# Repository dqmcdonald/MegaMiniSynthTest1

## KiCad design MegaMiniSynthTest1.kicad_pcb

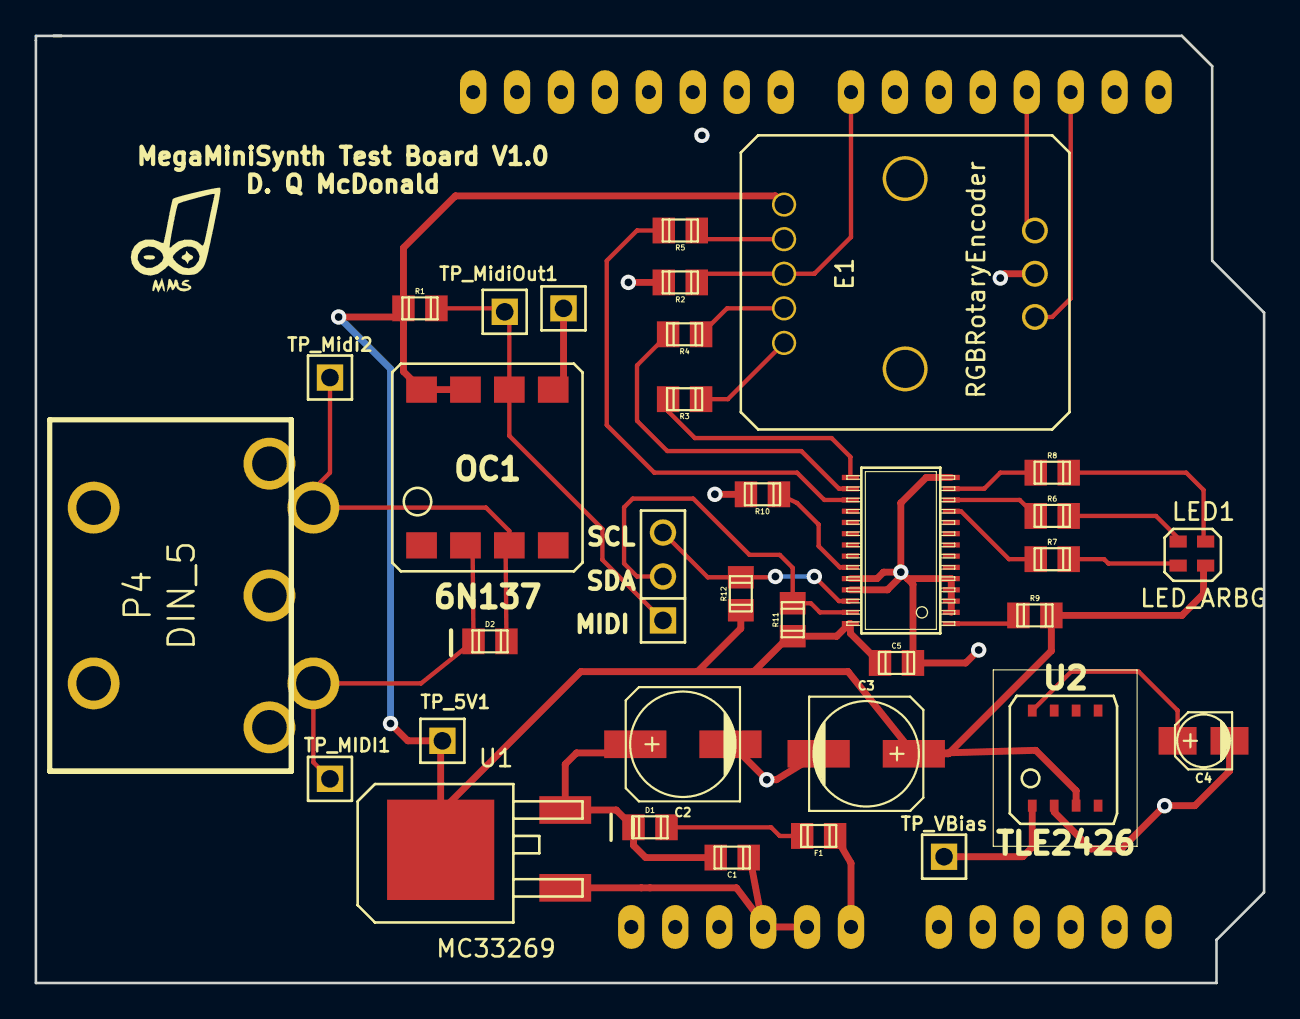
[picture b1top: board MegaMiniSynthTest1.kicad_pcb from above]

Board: 2 copper layers, 71.0 x 54.8 mm, 32 parts (0 on the bottom side), 26 nets.

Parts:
C1: 100n; c_0805
C2, C3: 47uF; c_elec_6.3x5.8
C4: 1uF; c_elec_3x5.3
C5: 100nf; c_0805
D1, D2: DIODE; c_0805
E1: RGBRotaryEncoder
F1: FERRITE; c_0805
LED1: LED_ARBG; SMDRGBLED
OC1: 6N137
P4: DIN_5
R1: 8k2; c_0805
R2, R10: 10K; c_0805
R3, R7, R8: 200; c_0805
R4, R5: 100; c_0805
R6: 300; c_0805
R9: 10k; c_0805
R11, R12: 4k7; c_0805
TP_5V1: PIN_ARRAY_1
TP_MIDI1: PIN_ARRAY_1
TP_Midi2: PIN_ARRAY_1
TP_MidiOut1: PIN_ARRAY_1
TP_VBias: PIN_ARRAY_1
U1: MC33269
U2: TLE2426
U3: PCA9685; -TSSOP28

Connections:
+5V: C3.1, C5.2, E1.5, LED1.1, OC1.7, OC1.8, R1.2, R9.1, R11.2, R12.2, TP_5V1.1, U1.2, U2.3, U3.28
Arduino7: E1.3, R2.2
GND: C1.2, C2.2, C3.2, C4.2, C5.1, E1.7, OC1.5, R2.1, R10.1, U1.1, U2.2, U3.2, U3.3, U3.4, U3.5, U3.14, U3.24, U3.25
unnamed: C4.1, U2.8
unnamed: D1.1, F1.1
unnamed: D2.1, OC1.3, P4.5, TP_Midi2.1
unnamed: D2.2, OC1.2, P4.4, TP_MIDI1.1
unnamed: E1.1, R3.2
unnamed: E1.2, R4.2
unnamed: E1.4, R5.2
unnamed: LED1.2, R6.1
unnamed: LED1.3, R8.1
unnamed: LED1.4, R7.1
unnamed: R3.1, U3.15
unnamed: R4.1, U3.16
unnamed: R5.1, U3.17
unnamed: R6.2, U3.12
unnamed: R7.2, U3.11
unnamed: R8.2, U3.13
unnamed: R9.2, U3.1
unnamed: R10.2, U3.23
SCL: R12.1, U3.26
SDA: R11.1, U3.27
Serial2: OC1.6, R1.1, TP_MidiOut1.1
VBias: TP_VBias.1, U2.1
VCC: C1.1, C2.1, D1.2, U1.3

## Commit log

2014-08-16 MegaMiniSynth Test Board 1
    Initial Commit
2014-08-16 Removed unneeded svg file
2014-08-16 Moved to new KiCad Version
2014-08-17 Board Layout basically done
    Added bypass cap for PWM driver
2014-08-20 Final version 1.0 as sent to OSHPark
2014-09-09 Added missing resistor for MIDI in
2014-09-10 Changed some resistor values
2014-09-10 Removed problematic microchip library
2014-09-19 Added PDF version of schematic
2014-09-19 Updated RGBEncoder library symbol
